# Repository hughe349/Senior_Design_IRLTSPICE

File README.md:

# IRLTSPICE - A Senior Design Project
 > *Zach DeNeve, Parker Hitchcock, Clayton Hughes, Micah Samuel*

## Overview

LTspice + irl = IRLTSPICE! IRLTSPICE is a configuratble analog circuit.

## Project Structure
The senior design project uses a monorepo architecture with the following sub-directories:
- `hardware/` Hardware schematics
- `firmware/` Microcontroller firmware
- `software/` On-PC software
- `evilware/` Evil Circuits and Code

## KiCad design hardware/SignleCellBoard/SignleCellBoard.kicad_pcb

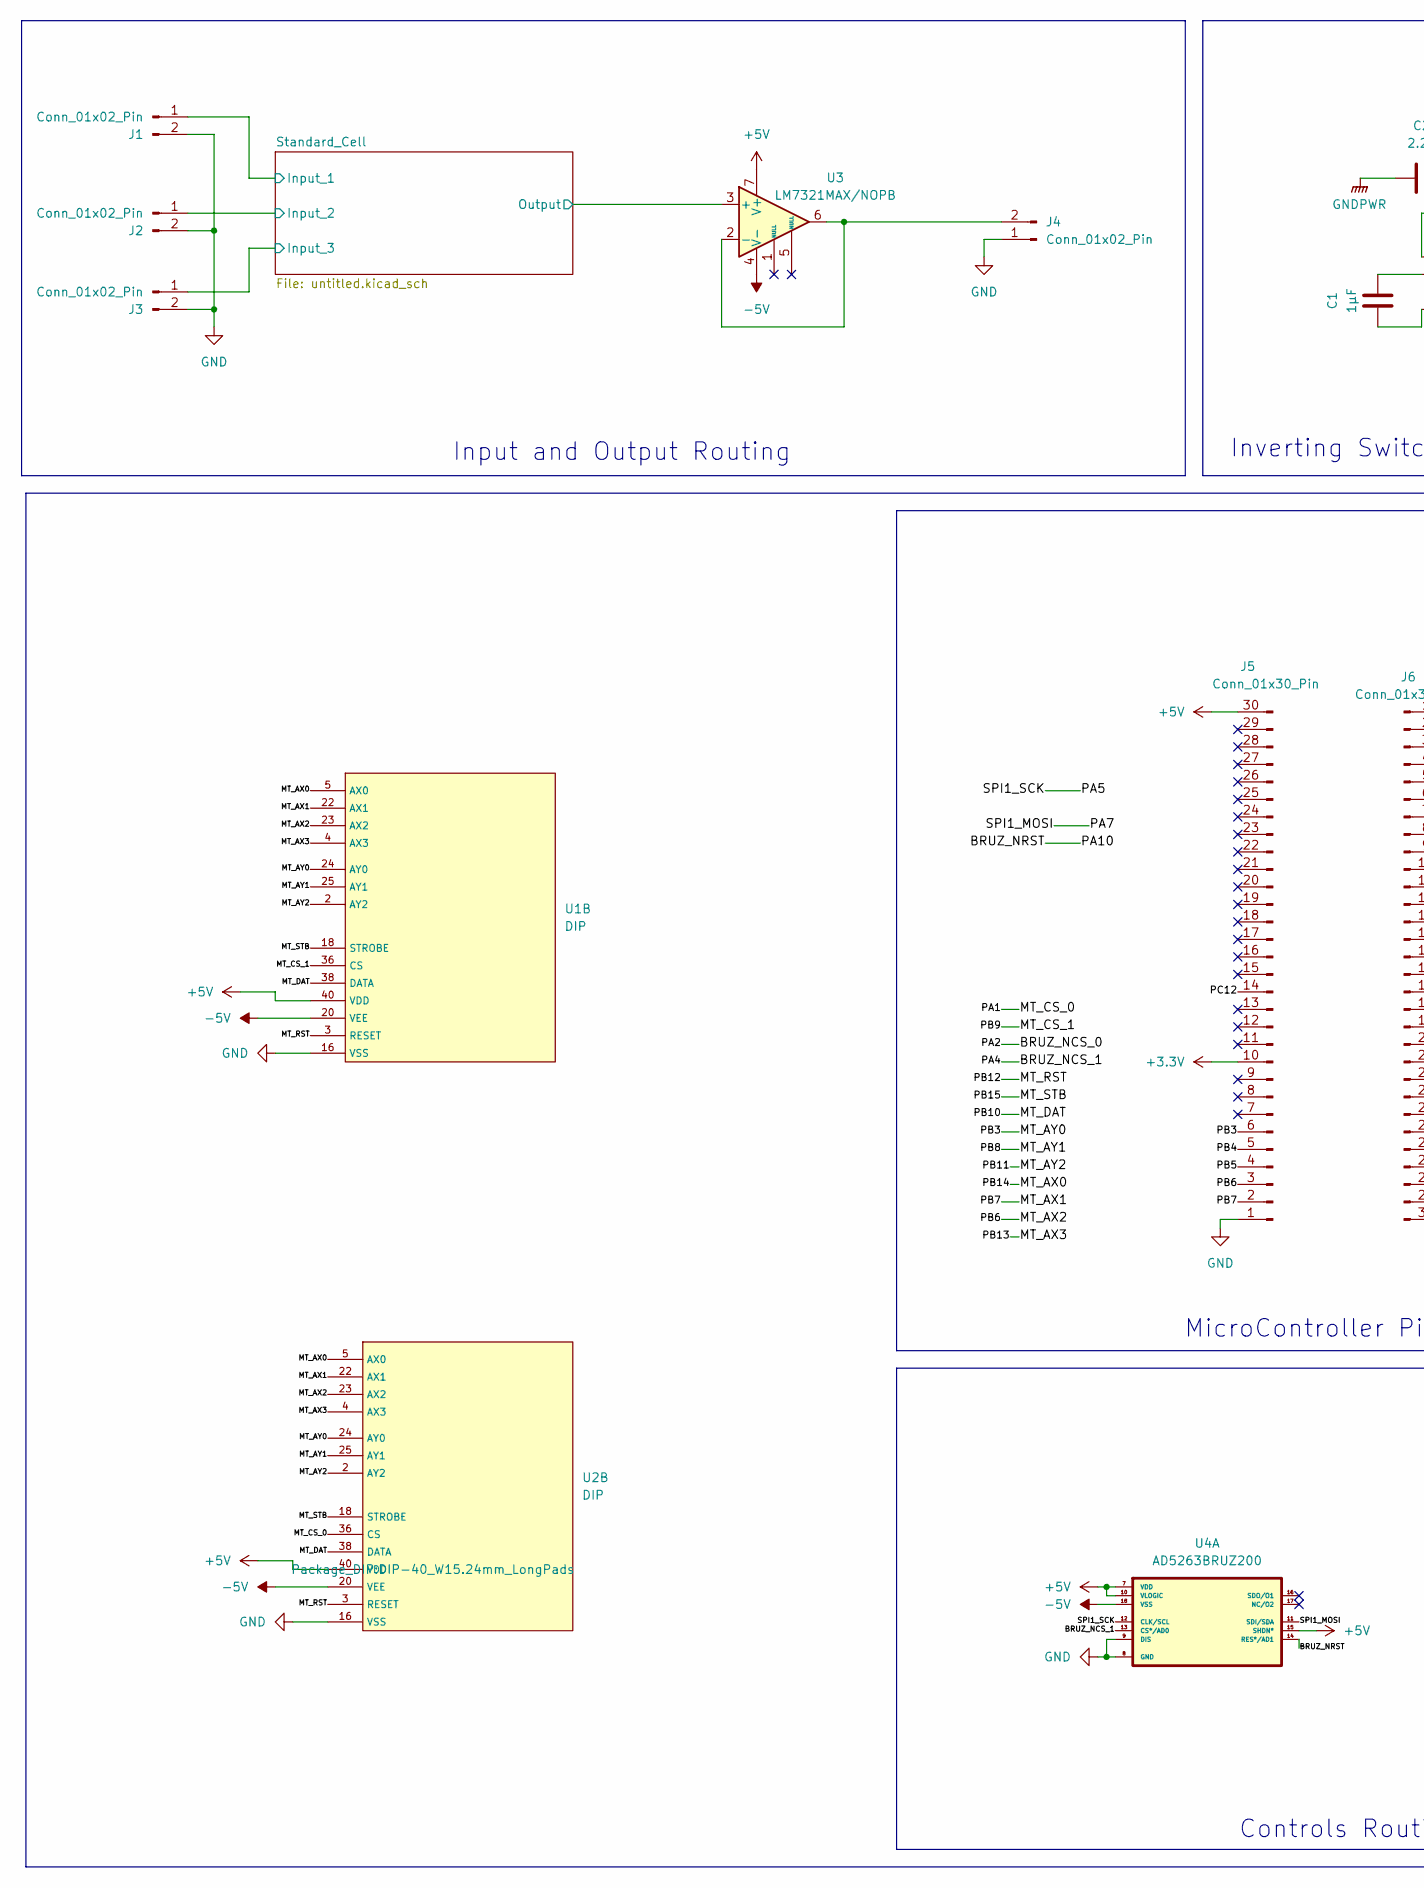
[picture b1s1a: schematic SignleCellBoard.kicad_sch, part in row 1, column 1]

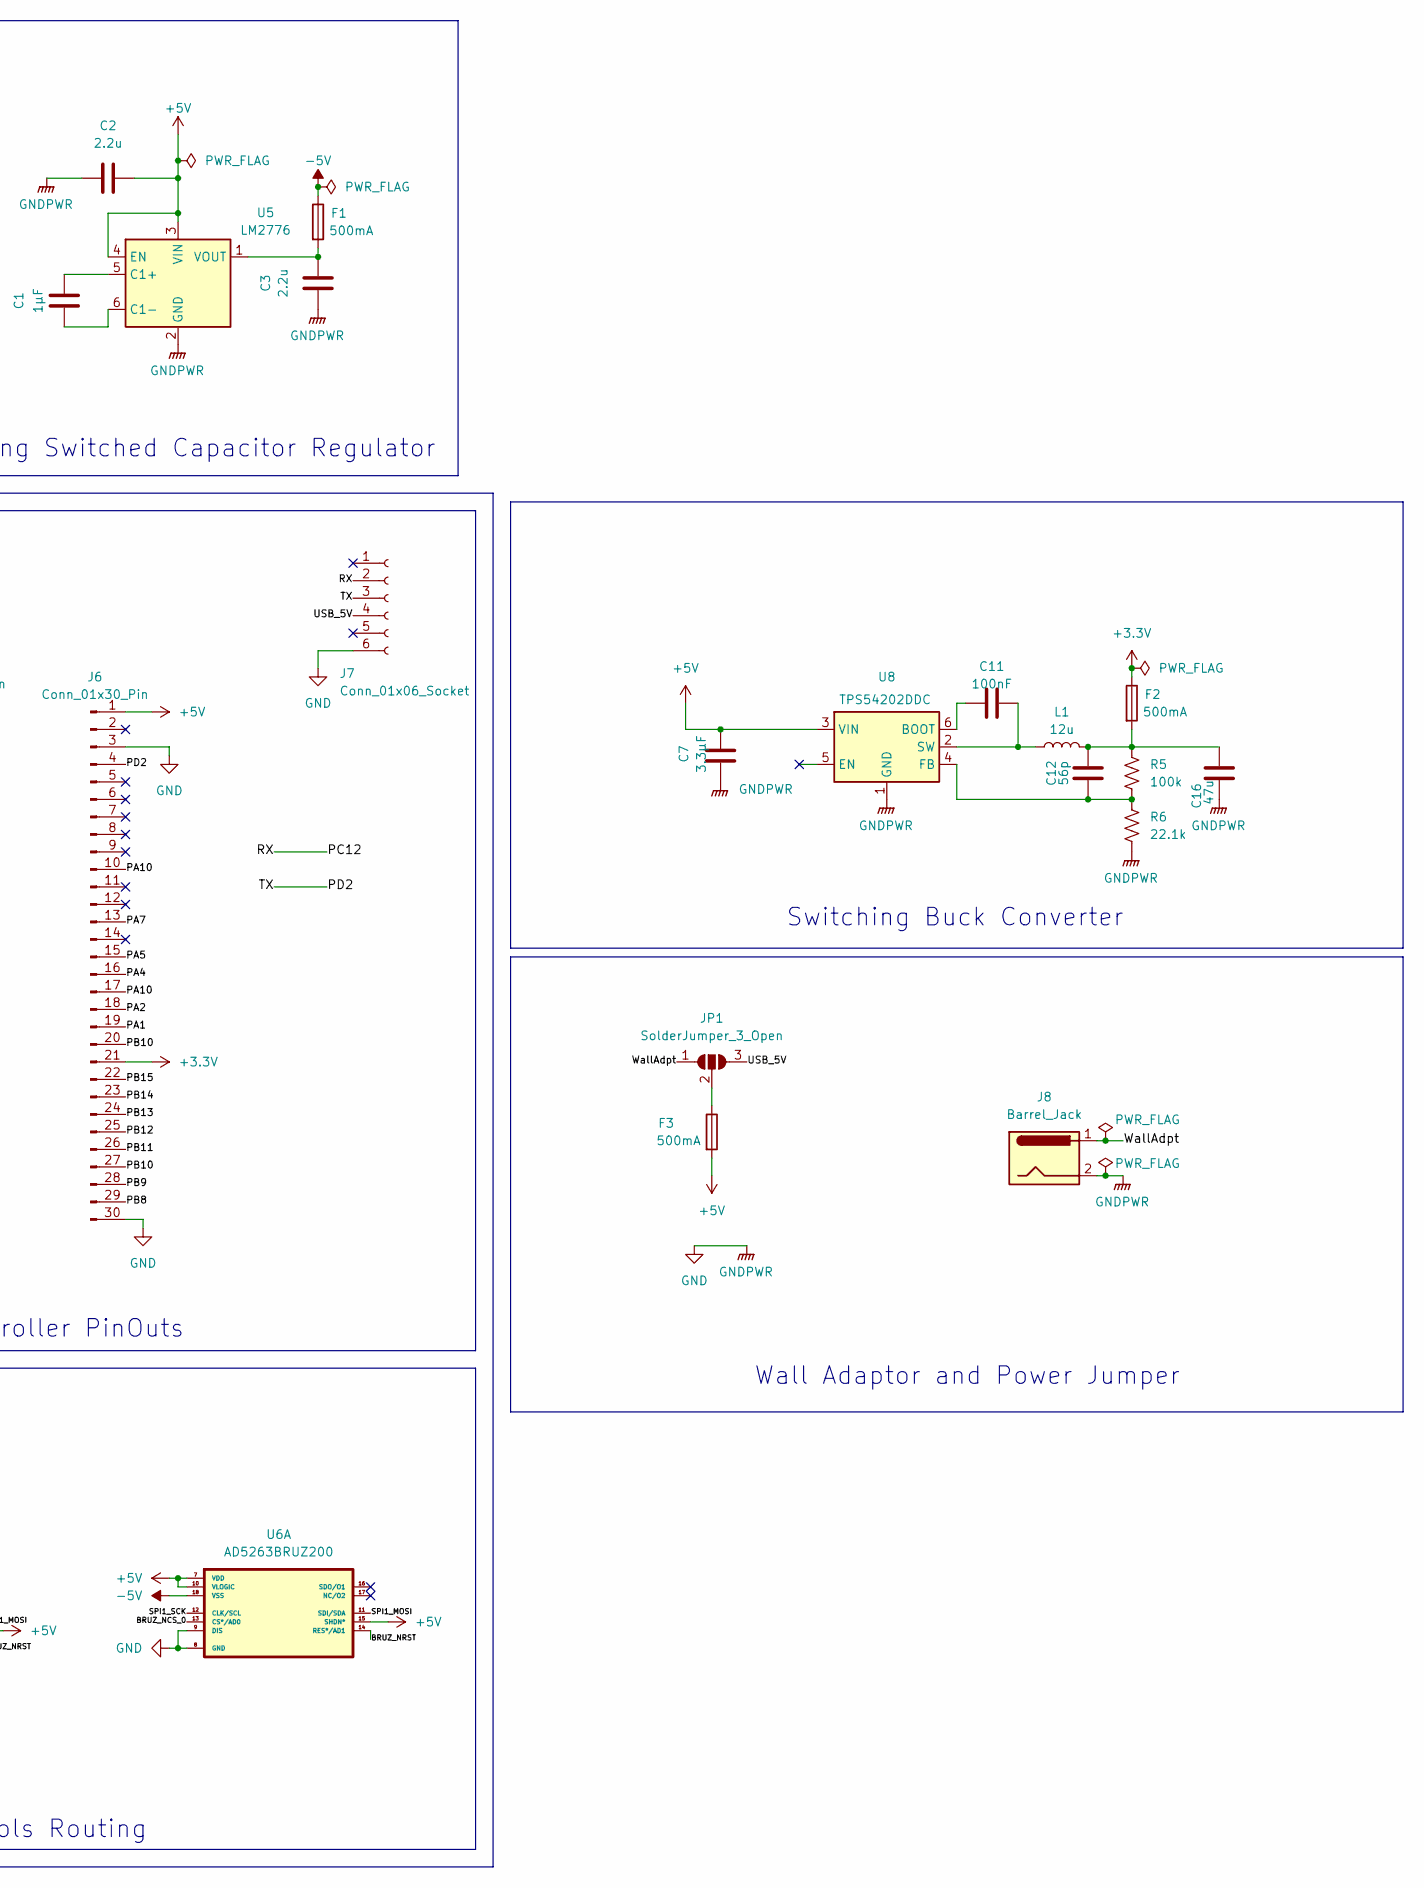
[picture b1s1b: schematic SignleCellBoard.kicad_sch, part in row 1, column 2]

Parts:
C1: 1µF; C_0603_1608Metric_Pad1.08x0.95mm_HandSolder
C2, C3: 2.2u; C_0603_1608Metric_Pad1.08x0.95mm_HandSolder
C7: 3.3µF; C_0805_2012Metric_Pad1.18x1.45mm_HandSolder
C11: 100nF; C_0805_2012Metric_Pad1.18x1.45mm_HandSolder
C12: 56p; C_0603_1608Metric
C16: 47u; C_0805_2012Metric_Pad1.18x1.45mm_HandSolder
F1, F2, F3: 500mA; Fuse_0603_1608Metric_Pad1.05x0.95mm_HandSolder
J1, J2, J3, J4: Conn_01x02_Pin; PinSocket_1x02_P2.54mm_Vertical
J5, J6: Conn_01x30_Pin; PinSocket_1x30_P2.54mm_Vertical
J7: Conn_01x06_Socket; PinSocket_1x06_P2.54mm_Vertical
J8: Barrel_Jack; BarrelJack_CUI_PJ-063AH_Horizontal
JP1: SolderJumper_3_Open; SolderJumper-3_P1.3mm_Open_Pad1.0x1.5mm_NumberLabels
L1: 12u; IND_4532-WE-PD2_WRE-L
R5: 100k; R_0402_1005Metric_Pad0.72x0.64mm_HandSolder
R6: 22.1k; R_0402_1005Metric_Pad0.72x0.64mm_HandSolder
U1, U2: DIP; DIP-40_W15.24mm_LongPads
U3: LM7321MAX/NOPB; SOIC-8_3.9x4.9mm_P1.27mm
U4, U6: AD5263BRUZ200; DIP-24_W15.24mm; MPN AD5263BRUZ200
U5: LM2776; PinHeader_1x06_P2.54mm_Vertical
U8: TPS54202DDC; PinHeader_1x06_P2.54mm_Vertical

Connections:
+3.3V: F2.1, J5.10, J6.21
+5V: C2.2, C7.2, F3.2, J5.30, J6.1, U1.40 (VDD), U2.40 (VDD), U3.7 (V+), U4.7 (VDD), U4.10 (VLOGIC), U4.15 (SHDN*), U5.3 (VIN), U5.4 (EN), U6.7 (VDD), U6.10 (VLOGIC), U6.15 (SHDN*), U8.3 (VIN); also elsewhere on the board
-5V: F1.1, U1.20 (VEE), U2.20 (VEE), U3.4 (V-), U4.18 (VSS), U6.18 (VSS); also elsewhere on the board
/BRUZ_NCS_0: J6.18, U6.13 (CS*/AD0)
/BRUZ_NCS_1: J6.16, U4.13 (CS*/AD0)
/BRUZ_NRST: J6.10, J6.17, U4.14 (RES*/AD1), U6.14 (RES*/AD1)
/MT_AX0: J6.23, U1.5 (AX0), U2.5 (AX0)
/MT_AX1: J5.2, U1.22 (AX1), U2.22 (AX1)
/MT_AX2: J5.3, U1.23 (AX2), U2.23 (AX2)
/MT_AX3: J6.24, U1.4 (AX3), U2.4 (AX3)
/MT_AY0: J5.6, U1.24 (AY0), U2.24 (AY0)
/MT_AY1: J6.29, U1.25 (AY1), U2.25 (AY1)
/MT_AY2: J6.26, U1.2 (AY2), U2.2 (AY2)
/MT_CS_0: J6.19, U2.36 (CS)
/MT_CS_1: J6.28, U1.36 (CS)
/MT_DAT: J6.20, J6.27, U1.38 (DATA), U2.38 (DATA)
/MT_RST: J6.25, U1.3 (RESET), U2.3 (RESET)
/MT_STB: J6.22, U1.18 (STROBE), U2.18 (STROBE)
/PA5: J6.15, U4.12 (CLK/SCL), U6.12 (CLK/SCL)
/PA7: J6.13, U4.11 (SDI/SDA), U6.11 (SDI/SDA)
/PB4: J5.5
/PB5: J5.4
/PC12: J5.14, J7.2
/PD2: J6.4, J7.3
/Standard_Cell/Y0: J1.1; also elsewhere on the board
/Standard_Cell/Y1: J2.1; also elsewhere on the board
/Standard_Cell/Y2: J3.1; also elsewhere on the board
/Standard_Cell/Y3: U3.3 (+); also elsewhere on the board
/USB_5V: J7.4, JP1.3 (B)
/WallAdpt: J8.1, JP1.1 (A)
GND: C2.1, C3.1, C7.1, C16.1, J1.2, J2.2, J3.2, J4.1, J5.1, J6.3, J6.30, J7.6, J8.2, R6.2, U1.16 (VSS), U2.16 (VSS), U4.8 (GND), U4.9 (DIS), U5.2 (GND), U6.8 (GND), U6.9 (DIS), U8.1 (GND); also elsewhere on the board
unnamed: C12.2, C16.2, F2.2, L1.2, R5.1
unnamed: J4.2, U3.2 (-), U3.6
unnamed: F3.1, JP1.2 (C)
unnamed: C1.2, U5.5 (C1+)
unnamed: C1.1, U5.6 (C1-)
unnamed: C3.2, F1.2, U5.1 (VOUT)
unnamed: C11.1, U8.6 (BOOT)
unnamed: C12.1, R5.2, R6.1, U8.4 (FB)
unnamed: C11.2, L1.1, U8.2 (SW)

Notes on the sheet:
MicroController PinOuts
Input and Output Routing
Wall Adaptor and Power Jumper
Inverting Switched Capacitor Regulator
Switching Buck Converter
Controls Routing

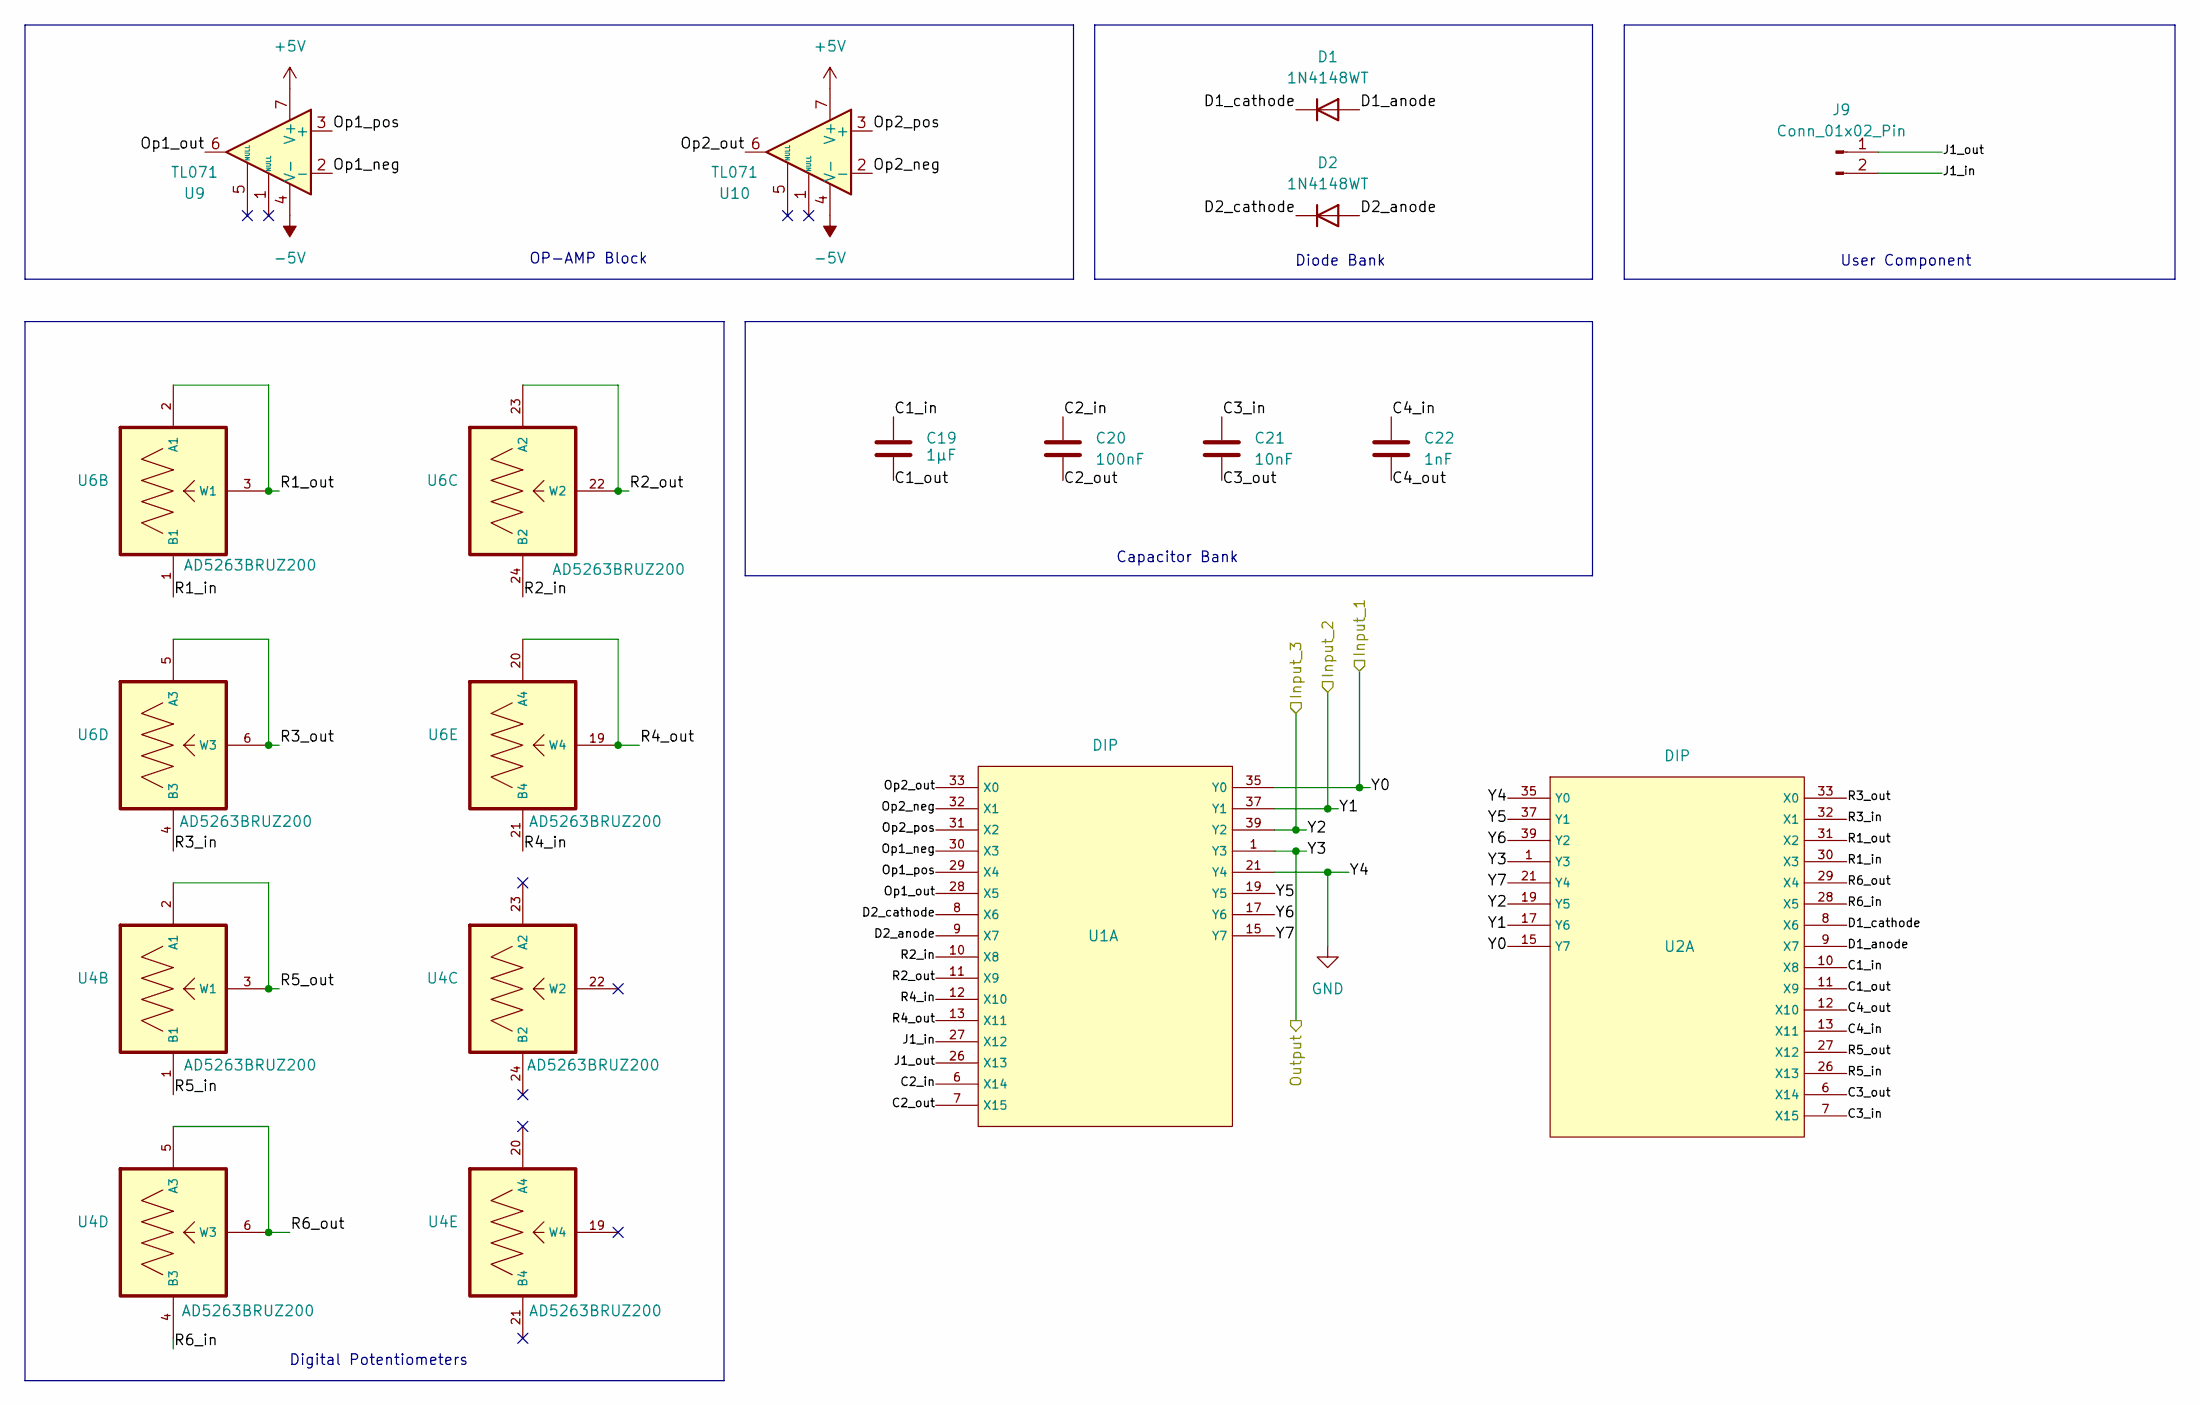
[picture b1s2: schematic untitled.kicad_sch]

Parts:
C19: 1µF; C_0603_1608Metric_Pad1.08x0.95mm_HandSolder
C20: 100nF; C_0603_1608Metric_Pad1.08x0.95mm_HandSolder
C21: 10nF; C_0603_1608Metric_Pad1.08x0.95mm_HandSolder
C22: 1nF; C_0603_1608Metric_Pad1.08x0.95mm_HandSolder
D1, D2: 1N4148WT; D_SOD-123
J9: Conn_01x02_Pin; PinSocket_1x02_P2.54mm_Vertical
U1, U2: DIP; DIP-40_W15.24mm_LongPads
U4, U6: AD5263BRUZ200; DIP-24_W15.24mm; MPN AD5263BRUZ200
U9, U10: TL071; SOIC-8_3.9x4.9mm_P1.27mm

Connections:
+5V: U9.7 (V+), U10.7 (V+); also elsewhere on the board
-5V: U9.4 (V-), U10.4 (V-); also elsewhere on the board
/Standard_Cell/C1_in: C19.1, U2.10 (X8)
/Standard_Cell/C1_out: C19.2, U2.11 (X9)
/Standard_Cell/C2_in: C20.1, U1.6 (X14)
/Standard_Cell/C2_out: C20.2, U1.7 (X15)
/Standard_Cell/C3_in: C21.1, U2.7 (X15)
/Standard_Cell/C3_out: C21.2, U2.6 (X14)
/Standard_Cell/C4_in: C22.1, U2.13 (X11)
/Standard_Cell/C4_out: C22.2, U2.12 (X10)
/Standard_Cell/D1_anode: D1.2 (A), U2.9 (X7)
/Standard_Cell/D1_cathode: D1.1 (K), U2.8 (X6)
/Standard_Cell/D2_anode: D2.2 (A), U1.9 (X7)
/Standard_Cell/D2_cathode: D2.1 (K), U1.8 (X6)
/Standard_Cell/J1_in: J9.2, U1.27 (X12)
/Standard_Cell/J1_out: J9.1, U1.26 (X13)
/Standard_Cell/Op1_neg: U1.30 (X3), U9.2 (-)
/Standard_Cell/Op1_out: U1.28 (X5), U9.6
/Standard_Cell/Op1_pos: U1.29 (X4), U9.3 (+)
/Standard_Cell/Op2_neg: U1.32 (X1), U10.2 (-)
/Standard_Cell/Op2_out: U1.33 (X0), U10.6
/Standard_Cell/Op2_pos: U1.31 (X2), U10.3 (+)
/Standard_Cell/R1_in: U2.30 (X3), U6.1 (B1)
/Standard_Cell/R1_out: U2.31 (X2), U6.2 (A1), U6.3 (W1)
/Standard_Cell/R2_in: U1.10 (X8), U6.24 (B2)
/Standard_Cell/R2_out: U1.11 (X9), U6.22 (W2), U6.23 (A2)
/Standard_Cell/R3_in: U2.32 (X1), U6.4 (B3)
/Standard_Cell/R3_out: U2.33 (X0), U6.5 (A3), U6.6 (W3)
/Standard_Cell/R4_in: U1.12 (X10), U6.21 (B4)
/Standard_Cell/R4_out: U1.13 (X11), U6.19 (W4), U6.20 (A4)
/Standard_Cell/R5_in: U2.26 (X13), U4.1 (B1)
/Standard_Cell/R5_out: U2.27 (X12), U4.2 (A1), U4.3 (W1)
/Standard_Cell/R6_in: U2.28 (X5), U4.4 (B3)
/Standard_Cell/R6_out: U2.29 (X4), U4.5 (A3), U4.6 (W3)
/Standard_Cell/Y0: U1.35 (Y0), U2.15 (Y7); also elsewhere on the board
/Standard_Cell/Y1: U1.37 (Y1), U2.17 (Y6); also elsewhere on the board
/Standard_Cell/Y2: U1.39 (Y2), U2.19 (Y5); also elsewhere on the board
/Standard_Cell/Y3: U1.1 (Y3), U2.1 (Y3); also elsewhere on the board
/Standard_Cell/Y5: U1.19 (Y5), U2.37 (Y1)
/Standard_Cell/Y6: U1.17 (Y6), U2.39 (Y2)
/Standard_Cell/Y7: U1.15 (Y7), U2.21 (Y4)
GND: U1.21 (Y4), U2.35 (Y0); also elsewhere on the board

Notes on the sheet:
Capacitor Bank
Digital Potentiometers
User Component
Diode Bank
OP-AMP Block

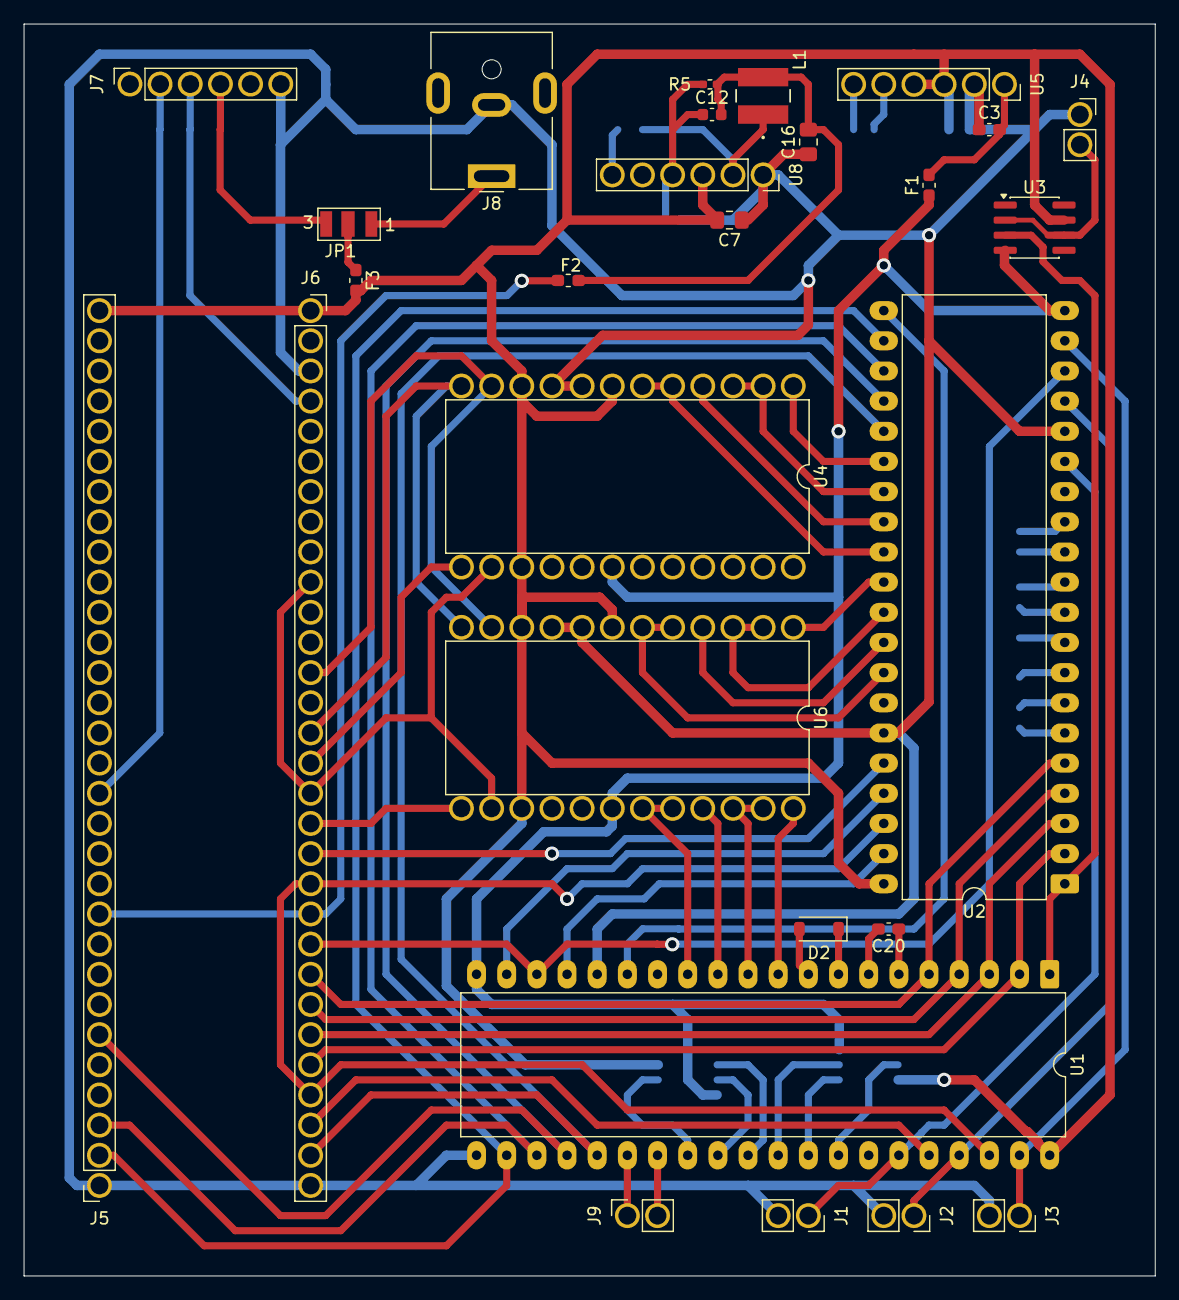
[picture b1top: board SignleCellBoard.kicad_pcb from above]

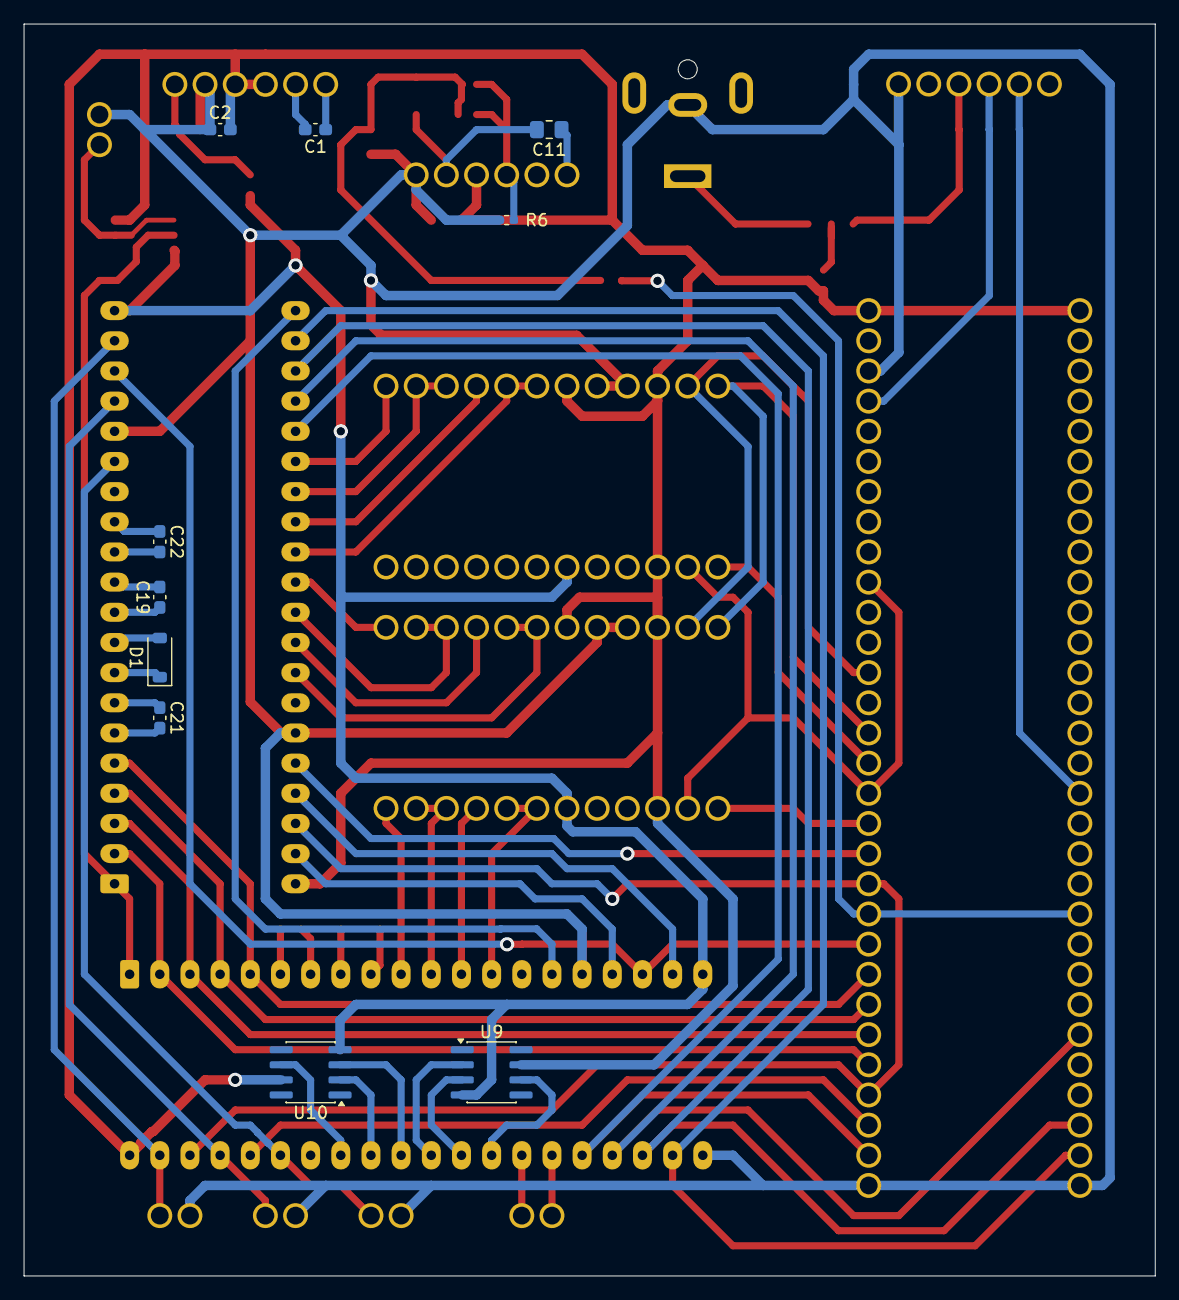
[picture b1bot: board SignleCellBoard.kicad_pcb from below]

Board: 2 copper layers, 95.2 x 105.4 mm, 38 parts (10 on the bottom side), 73 nets.

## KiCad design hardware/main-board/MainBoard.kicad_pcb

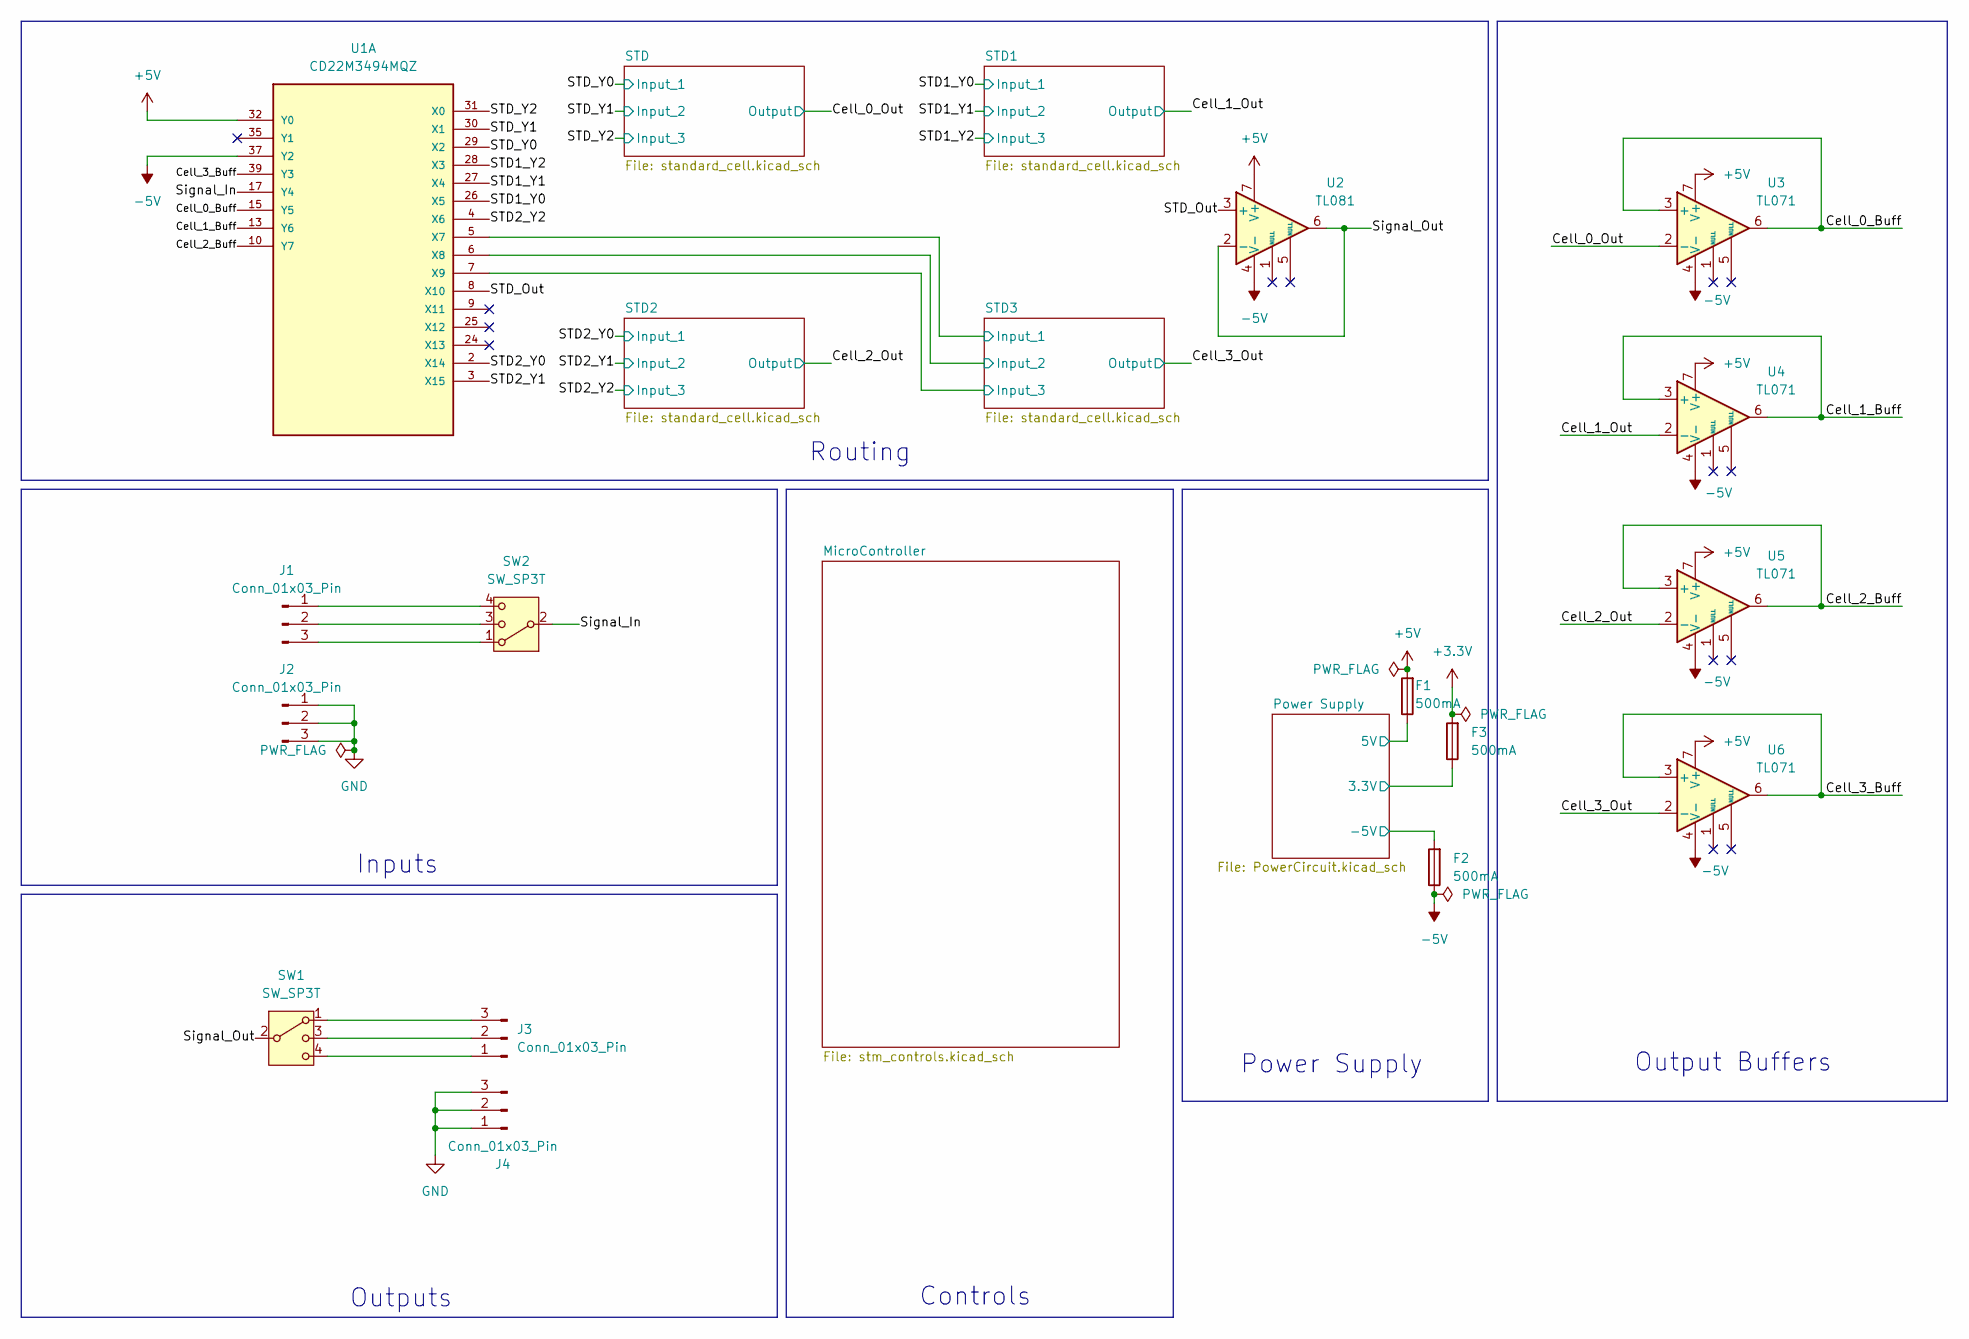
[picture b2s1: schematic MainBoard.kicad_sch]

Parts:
F1, F2, F3: 500mA; Fuse_0603_1608Metric_Pad1.05x0.95mm_HandSolder
J1, J2, J3, J4: Conn_01x03_Pin; PinHeader_1x03_P2.54mm_Vertical
SW1, SW2: SW_SP3T; SW_Slide_SP3T_Straight_CK_OS103012MU1QP1
U1: CD22M3494MQZ; PLCC44_16P66X16P66_INR-M; PARTREV September 2011
U2: TL081; SOIC-8_3.9x4.9mm_P1.27mm
U3, U4, U5, U6: TL071; SOIC-8_3.9x4.9mm_P1.27mm

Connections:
+3.3V: F3.2; also elsewhere on the board
+5V: F1.2, U1.32 (Y0), U2.7 (V+), U3.7 (V+), U4.7 (V+), U5.7 (V+), U6.7 (V+); also elsewhere on the board
-5V: F2.1, U1.37 (Y2), U2.4 (V-), U3.4 (V-), U4.4 (V-), U5.4 (V-), U6.4 (V-); also elsewhere on the board
/Cell_0_Buff: U1.15 (Y5), U3.3 (+), U3.6
/Cell_0_Out: U3.2 (-); also elsewhere on the board
/Cell_1_Buff: U1.13 (Y6), U4.3 (+), U4.6
/Cell_1_Out: U4.2 (-); also elsewhere on the board
/Cell_2_Buff: U1.10 (Y7), U5.3 (+), U5.6
/Cell_2_Out: U5.2 (-); also elsewhere on the board
/Cell_3_Buff: U1.39 (Y3), U6.3 (+), U6.6
/Cell_3_Out: U6.2 (-); also elsewhere on the board
/Power Supply/3.3V: F3.1; also elsewhere on the board
/Power Supply/5V: F1.1; also elsewhere on the board
/Power Supply/-5V: F2.2; also elsewhere on the board
/STD1_Y0: U1.26 (X5); also elsewhere on the board
/STD1_Y1: U1.27 (X4); also elsewhere on the board
/STD1_Y2: U1.28 (X3); also elsewhere on the board
/STD2_Y0: U1.2 (X14); also elsewhere on the board
/STD2_Y1: U1.3 (X15); also elsewhere on the board
/STD2_Y2: U1.4 (X6); also elsewhere on the board
/STD3/Y0: U1.5 (X7); also elsewhere on the board
/STD3/Y1: U1.6 (X8); also elsewhere on the board
/STD3/Y2: U1.7 (X9); also elsewhere on the board
/STD_Out: U1.8 (X10), U2.3 (+)
/STD_Y0: U1.29 (X2); also elsewhere on the board
/STD_Y1: U1.30 (X1); also elsewhere on the board
/STD_Y2: U1.31 (X0); also elsewhere on the board
/Signal_In: SW2.2, U1.17 (Y4)
/Signal_Out: SW1.2, U2.2 (-), U2.6
GND: J2.1, J2.2, J2.3, J4.1, J4.2, J4.3; also elsewhere on the board
unnamed: J1.1, SW2.4
unnamed: J1.2, SW2.3
unnamed: J1.3, SW2.1
unnamed: J3.1, SW1.4
unnamed: J3.2, SW1.3
unnamed: J3.3, SW1.1

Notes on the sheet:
Inputs
Controls
Outputs
Power Supply
Routing
Output Buffers
